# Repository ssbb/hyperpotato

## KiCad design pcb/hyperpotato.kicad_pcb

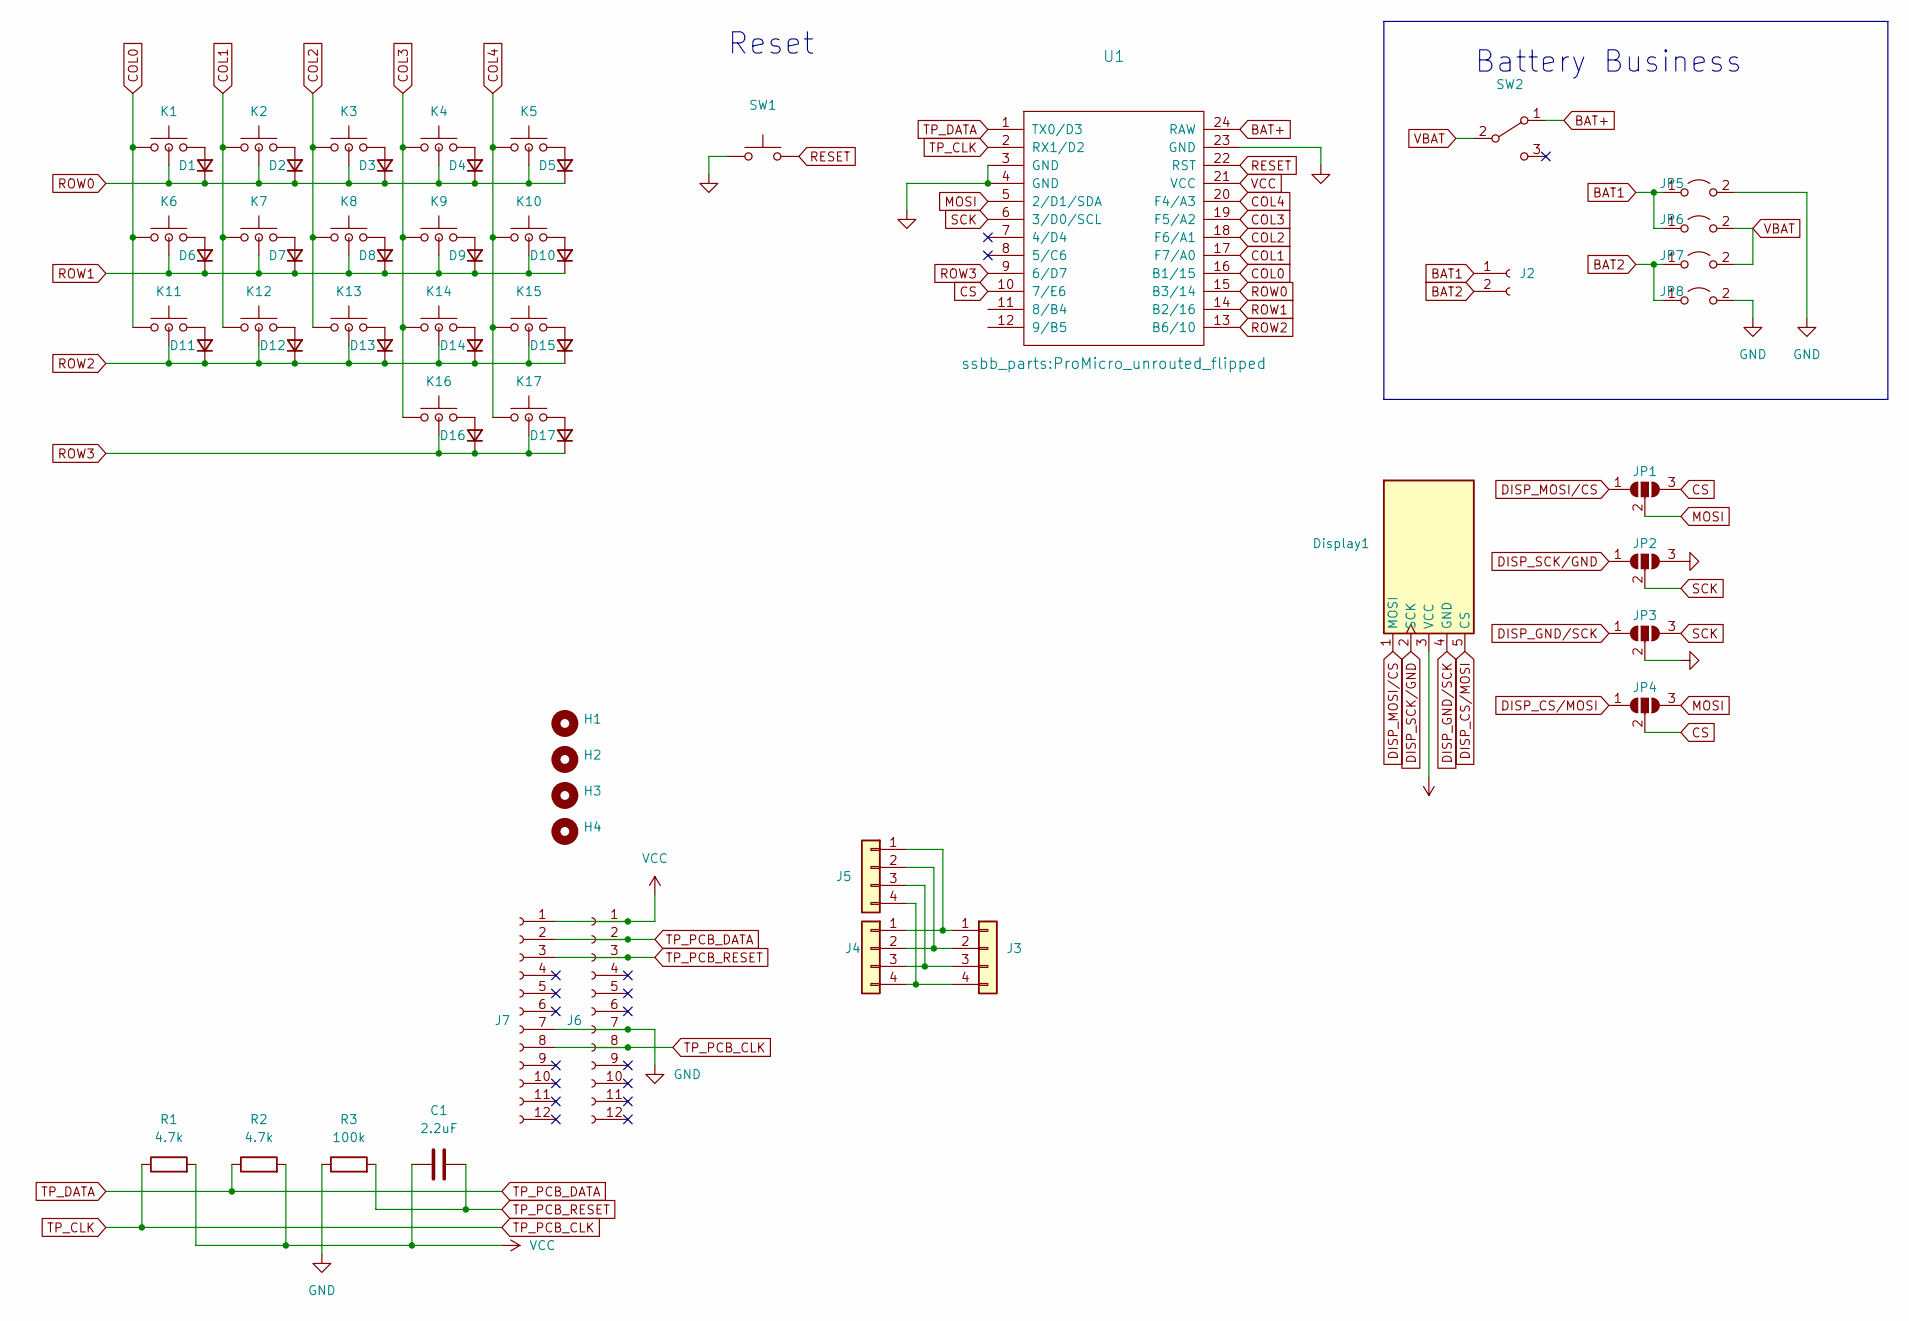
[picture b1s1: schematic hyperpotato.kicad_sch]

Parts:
C1: 2.2uF; C_reversible
D1, D2, D3, D4, D5, D6, D7, D8, D9, D10, D11, D12, D13, D14, D15, D16, D17: D_Small; Diode_SOD123
Display1: nice!view; nice_view
H1, H2, H3, H4: MountingHole; MountingHole_SolderNut
J2: Conn_01x02_Socket; JST_PH_S2B-PH-K_1x02_P2.00mm_Horizontal
J3: Conn_01x04; Trackpoint_Connector_Reversible
J4, J5: Conn_01x04; Trackpoint_Connector
J6, J7: Conn_01x12_Socket; Trackpoint_PCB_Connector
JP1, JP2, JP3, JP4: SolderJumper_3_Open; solder_jumper_reversible
JP5, JP6, JP7, JP8: Jumper_2_Open; SolderJumper-2_P1.3mm_Open_Pad1.0x1.5mm
K1, K2, K3, K4, K5, K6, K7, K8, K9, K10, K11, K12, K13, K14, K16: SW_Push; V1_V2_HS_reversible_plated
K15: SW_Push; V1_V2_HS_reversible_plated_alt
K17: SW_Push; V1_V2_HS_reversible_plated_no_fix_pin
R1, R2: 4.7k; R_reversible
R3: 100k; R_reversible
SW1: SW_Push; Panasonic_EVQPUL_EVQPUC
SW2: SW_SPDT; SW_SPDT_PCM12_reversible
U1: ProMicro; ProMicro_unrouted_flipped

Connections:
BAT1: J2.1, JP5.1 (A), JP6.1 (A)
BAT2: J2.2, JP7.1 (A), JP8.1 (A)
BAT+: SW2.1 (A), U1.24 (RAW)
COL0: K1.1, K6.1, K11.1, U1.16 (B1/15)
COL1: K2.1, K7.1, K12.1, U1.17 (F7/A0)
COL2: K3.1, K8.1, K13.1, U1.18 (F6/A1)
COL3: K4.1, K9.1, K14.1, K16.1, U1.19 (F5/A2)
COL4: K5.1, K10.1, K15.2, K17.1, U1.20 (F4/A3)
CS: JP1.3 (B), JP4.2 (C), U1.10 (7/E6)
DISP_CS/MOSI: Display1.5 (CS), JP4.1 (A)
DISP_GND/SCK: Display1.4 (GND), JP3.1 (A)
DISP_MOSI/CS: Display1.1 (MOSI), JP1.1 (A)
DISP_SCK/GND: Display1.2 (SCK), JP2.1 (A)
GND: J6.7, J7.7, JP2.3 (B), JP3.2 (C), JP5.2 (B), JP8.2 (B), R3.1, SW1.1, U1.3 (GND), U1.4 (GND), U1.23 (GND)
MOSI: JP1.2 (C), JP4.3 (B), U1.5 (2/D1/SDA)
unnamed: D1.2 (A), K1.2
unnamed: D2.2 (A), K2.2
unnamed: D3.2 (A), K3.2
unnamed: D4.2 (A), K4.2
unnamed: D5.2 (A), K5.2
unnamed: D6.2 (A), K6.2
unnamed: D7.2 (A), K7.2
unnamed: D8.2 (A), K8.2
unnamed: D9.2 (A), K9.2
unnamed: D10.2 (A), K10.2
unnamed: D11.2 (A), K11.2
unnamed: D12.2 (A), K12.2
unnamed: D13.2 (A), K13.2
unnamed: D14.2 (A), K14.2
unnamed: D15.2 (A), K15.1
unnamed: D16.2 (A), K16.2
unnamed: D17.2 (A), K17.2
unnamed: J3.1, J4.1, J5.1
unnamed: J3.2, J4.2, J5.2
unnamed: J3.3, J4.3, J5.3
unnamed: J3.4, J4.4, J5.4
RESET: SW1.2, U1.22 (RST)
ROW0: D1.1 (K), D2.1 (K), D3.1 (K), D4.1 (K), D5.1 (K), K1.3, K2.3, K3.3, K4.3, K5.3, U1.15 (B3/14)
ROW1: D6.1 (K), D7.1 (K), D8.1 (K), D9.1 (K), D10.1 (K), K6.3, K7.3, K8.3, K9.3, K10.3, U1.14 (B2/16)
ROW2: D11.1 (K), D12.1 (K), D13.1 (K), D14.1 (K), D15.1 (K), K11.3, K12.3, K13.3, K14.3, K15.3, U1.13 (B6/10)
ROW3: D16.1 (K), D17.1 (K), K16.3, K17.3, U1.9 (6/D7)
SCK: JP2.2 (C), JP3.3 (B), U1.6 (3/D0/SCL)
TP_CLK: J6.8, J7.8, R1.1, U1.2 (RX1/D2)
TP_DATA: J6.2, J7.2, R2.1, U1.1 (TX0/D3)
TP_PCB_RESET: C1.2, J6.3, J7.3, R3.2
VBAT: JP6.2 (B), JP7.2 (B), SW2.2 (B)
VCC: C1.1, Display1.3 (VCC), J6.1, J7.1, R1.2, R2.2, U1.21 (VCC)

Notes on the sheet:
Reset
Battery Business

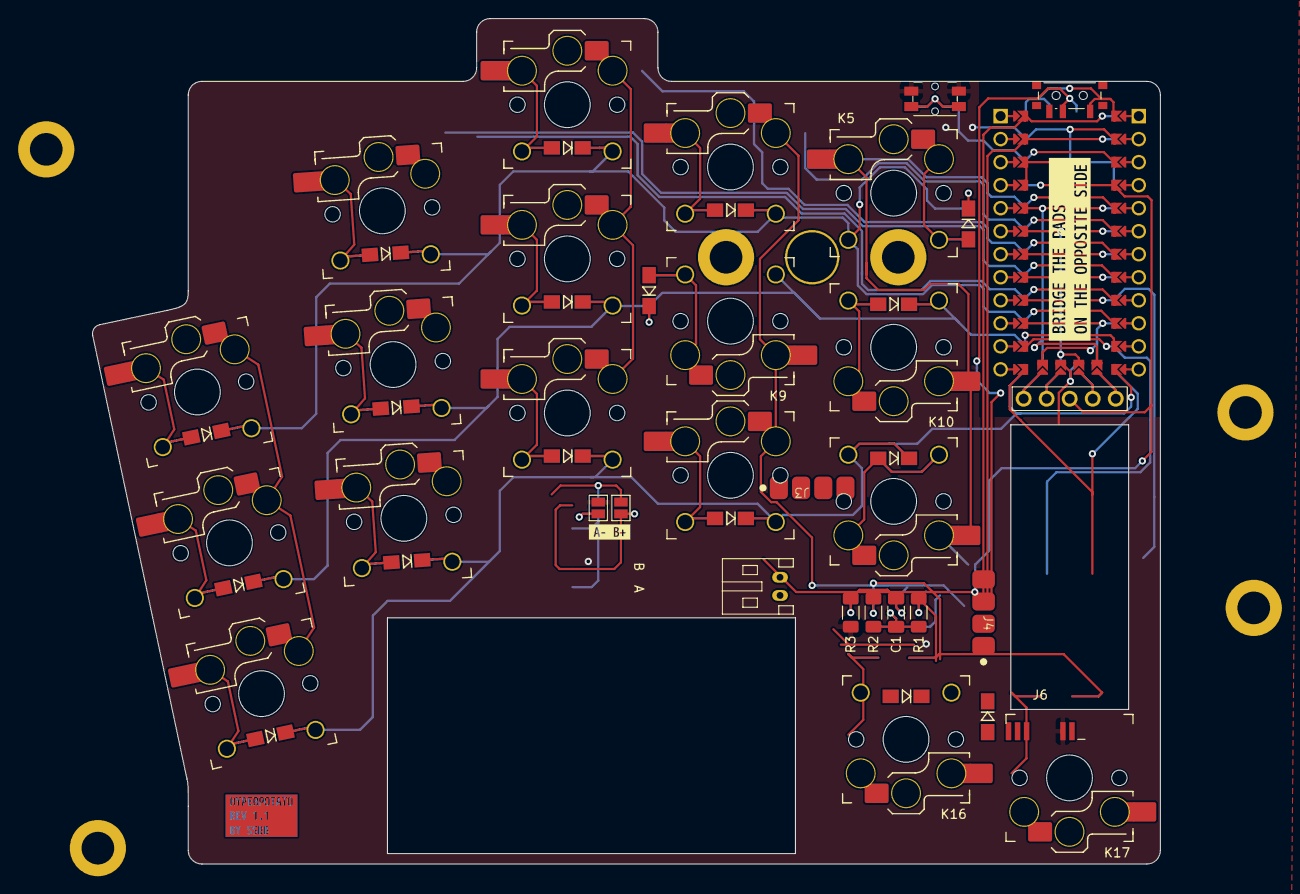
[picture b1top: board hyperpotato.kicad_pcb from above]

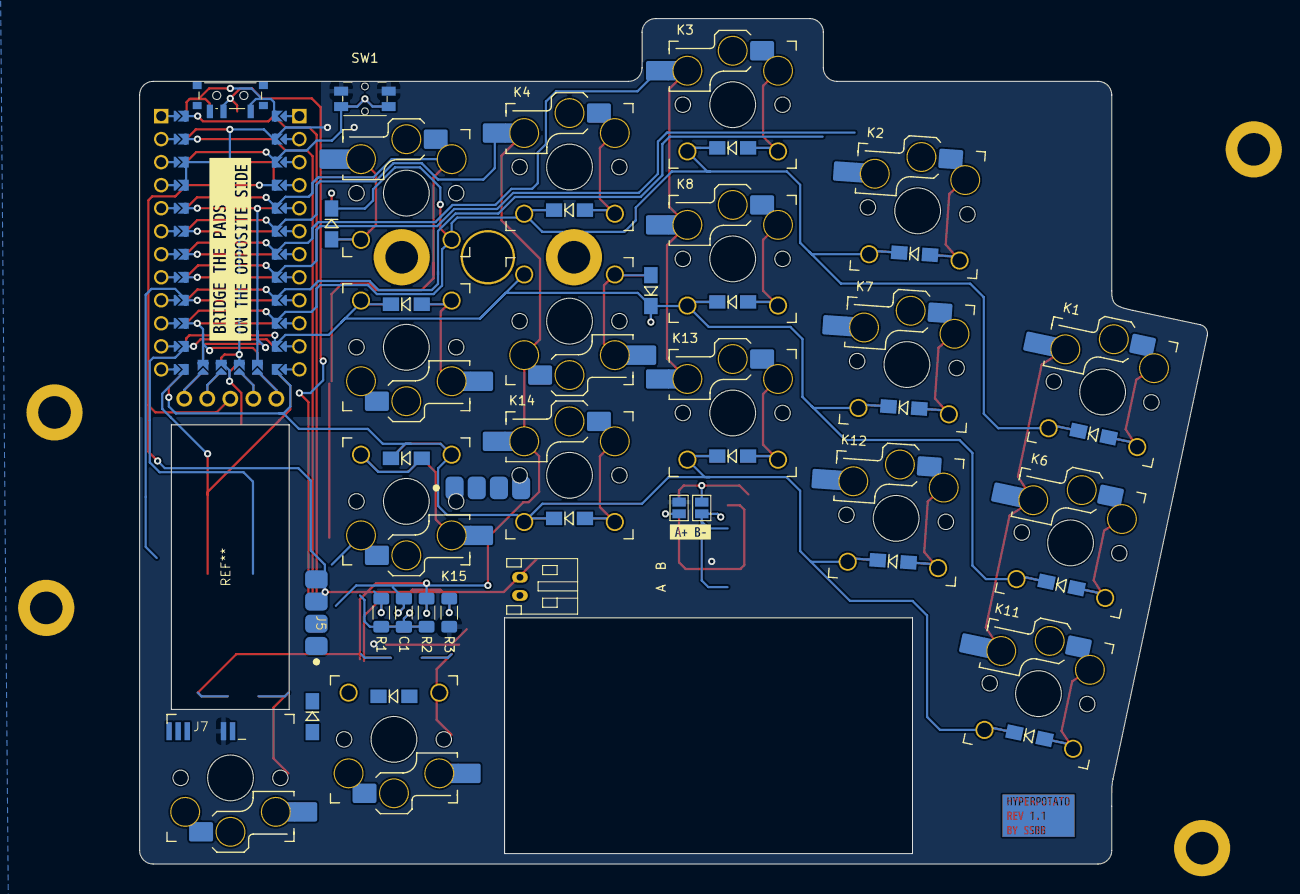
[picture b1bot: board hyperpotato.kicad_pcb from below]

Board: 2 copper layers, 117.8 x 93.3 mm, 67 parts (29 on the bottom side), 47 nets.

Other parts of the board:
TP1: trackpoint_mount_t430
kibuzzard-65B49B7B, kibuzzard-65B49B7B#2: G***; kibuzzard-65B49B7B
kibuzzard-65B482C9: G***; kibuzzard-65B482C9
kibuzzard-65B4826D: G***; kibuzzard-65B4826D
kibuzzard-65CD786D: G***; kibuzzard-65CD786D
kibuzzard-65CD7866: G***; kibuzzard-65CD7866

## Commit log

2024-01-27 Add keycaps
2024-01-27 Add binary flag for STL keycaps
2024-02-24 WIP re-layout
2024-03-03 WIP trackpoint mounting
2024-03-03 Change outlines for the new stagger/splay
2024-03-03 Remove encoder
2024-03-03 Make outline a bit smaller
2024-03-03 Distribute components
2024-03-04 Finish v2
2024-03-09 Remove out of sync plates
2024-04-08 Prepare rev1.3
2024-04-21 Revert "Prepare rev1.3"
    This reverts commit 189d012c5a395af6f6aed353e3fd92b88b9e8c79.
2024-05-02 Add PG1232 footprint
2024-05-04 Quick and dirty tucky thumbs pcb
2024-05-05 Quick and dirty choc mini version
